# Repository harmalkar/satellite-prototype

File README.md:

# satellite-prototype
This repository contains all the files relating to BPP payload for SEDS UMD.

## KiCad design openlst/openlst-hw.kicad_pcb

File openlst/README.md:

# OpenLST Development/BPP Board

OpenLST board for SEDS@UMD modified by Nathan Kerns. The latest version of Kicad 6 Nightlies is required to view or modify the design. Recent pdf exports of the PCB and schematic are available in the pdf folder, but may not be completely up to date.

[Interactive BOM](https://harmalkar.github.io/satellite-prototype/ibom.html)

## BOM

BOM is automatically generated in KiCAD using "bom_csv_grouped_by_value" script, and manually separated into formats seen in bom folder. `openlst-bom.csv` contains entire BOM, `openlst-bom-digikey.csv` contains Digikey components, and `openlst-bom-mouser.csv` contains Mouser components.

## Power Budgets

3.3 V - 85 mA

* CC1110 - 50 mA max
* ASFL1-27MHz - 15 mA max
* TLV803S - 15 mA max
* PE4259 - <1 mA
* RFFM6404 - <1 mA

4.2 V - 600 mA

* RFFM6404 - 600 mA max

## Frequency Range

430-445 MHz

* CC1110 - 391-464 MHz
* SF2446E - 425-445 MHz
* RFFM6404 - 430-450 MHz

## Temperature Range

Constraining component is ASFL1-27MHz at -20 to 70 C

## PCB

Layers
* F.Cu - GND plane + signals
* In1.Cu - GND plane
* In2.Cu - Power planes
* B.Cu - GND plane + signals

50 ohm traces
* 6 mil (0.15 mm) clearance
* 13.4 mil (0.34 mm) width
* Via fence on 50x50 mil (1.27x1.27 mm) grid

Other traces
* 0.2 mm (8 mil) signal traces
* 0.3 mm (12 mil) power traces
* Power planes for high current paths

## Dimensions

* Board size: 50x43mm (not including SMA connector)
* Hole pattern: 43x36mm, M3 clearance hole (3.2mm diameter), screw head up to 6.5mm diameter

# Original readme

OpenLST Reference Hardware
==========================

This repository contains a KiCad project with a hardware reference
implementation for the OpenLST.  This design is a simplified version
of the Texas Instruments CC1110 432 MHz reference design.  A 1 watt
power amplifier module has been added to increase operating range.
The design is intended for use at 437 MHz, however, it may be modified
for use at other frequencies.

The user is responsible for obtaining and maintaining the necessary
license to operate this radio.  The example project uses frequencies
in the US Amateur Radio UHF band. Transmissions in this band require a
valid FCC license and compliance with CFR Part 97.

Contents
--------

This repository contains the following items:

  * [KiCAD 4.0](http://kicad-pcb.org/) project with self-contained part library
  * [Schematic](pdf/openlst-hw.pdf) in PDF form
  * [Bill of materials](bom/) with ordering information for components
  * [Gerber files](gerber/) for PCB fabrication

License & Legal Information
---------------------------

Copyright 2018 Planet Labs Inc. This work is licensed under a
Creative Commons Attribution-ShareAlike 4.0 International License.

This document may contain technology or software the export of which
is or may be restricted by the Export Administration Act and the
Export Administration Regulations (EAR), 15 C.F.R. parts
730-774. Diversion contrary to U.S. law is prohibited.

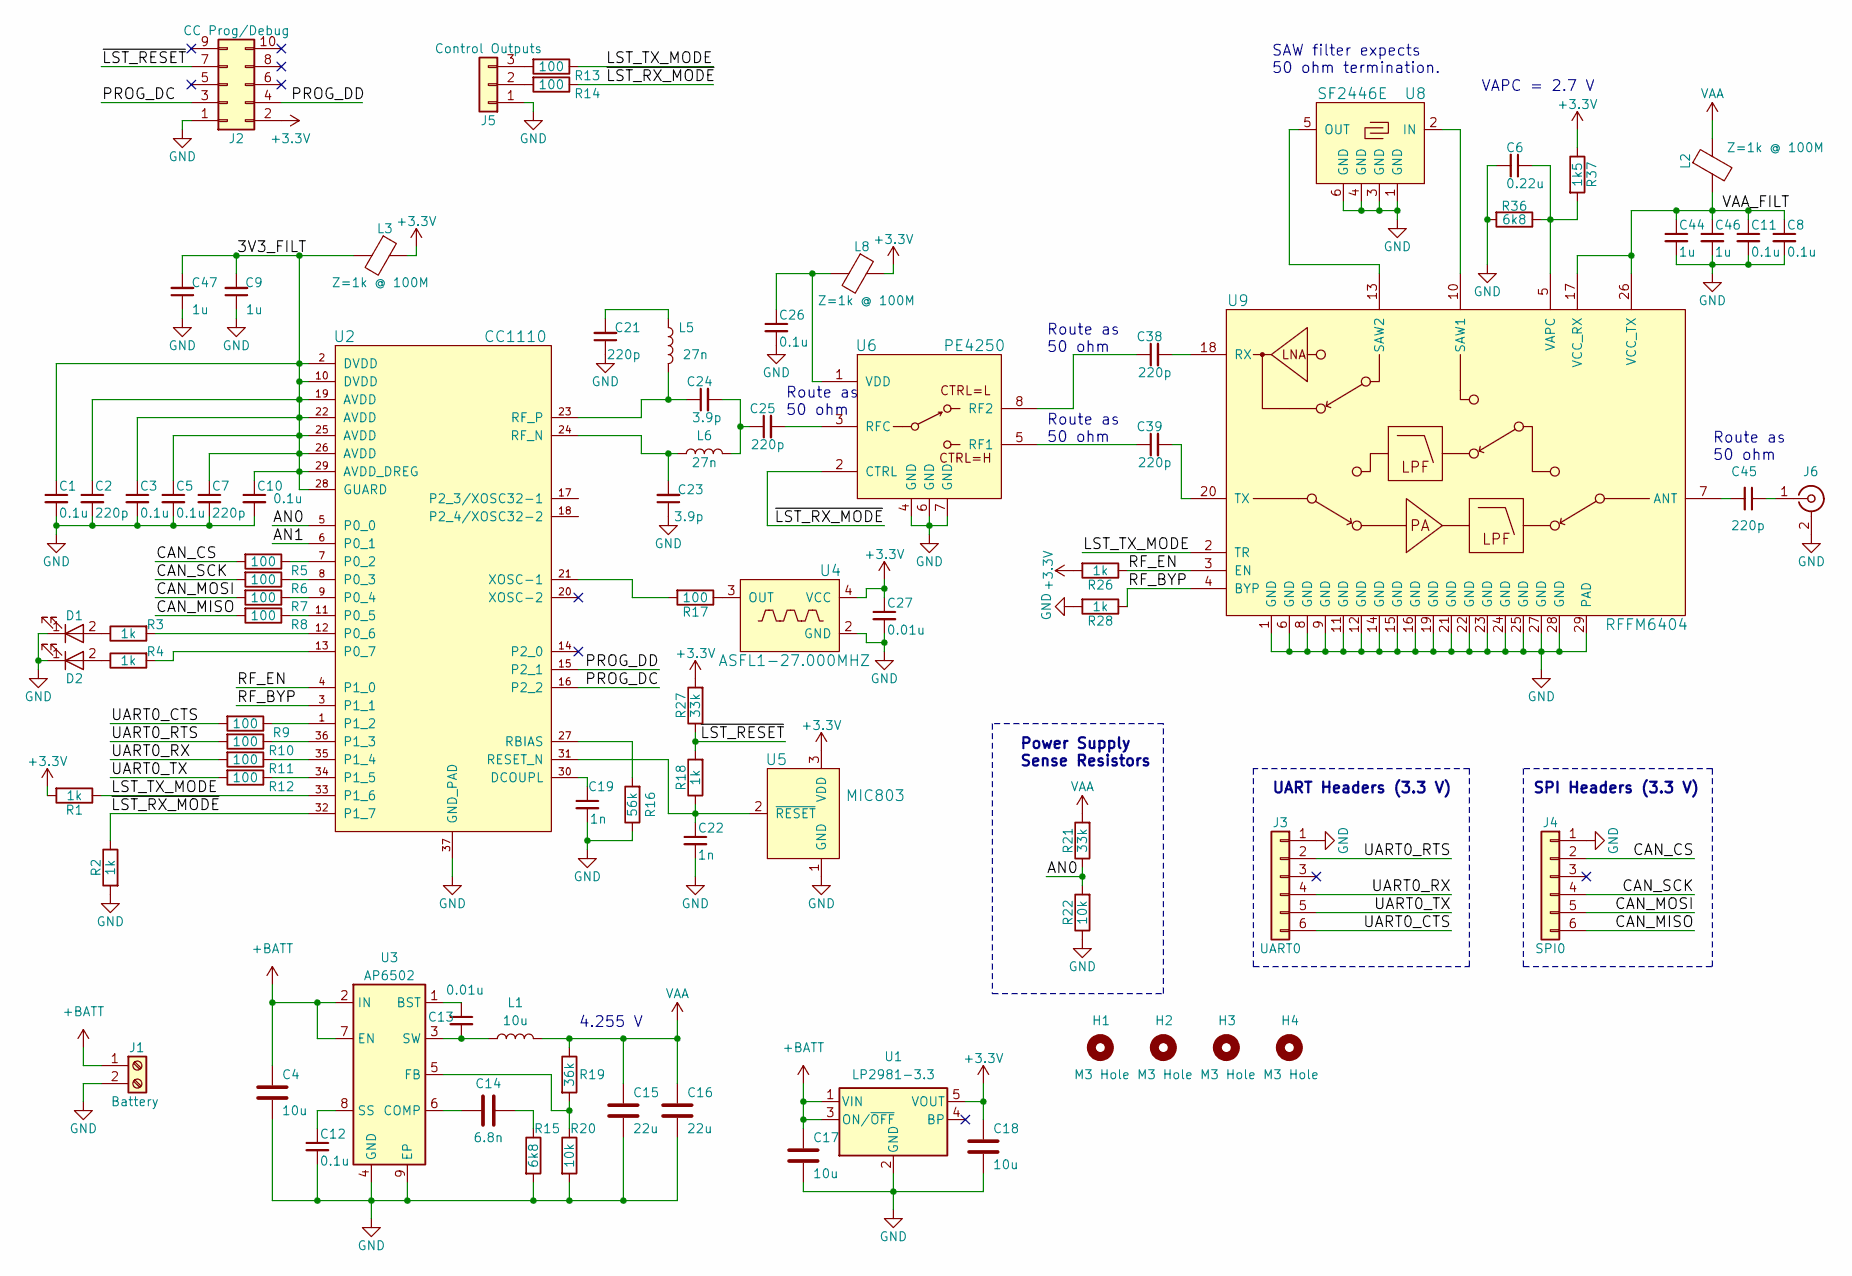
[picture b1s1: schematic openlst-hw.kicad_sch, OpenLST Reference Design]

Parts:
C1, C3, C5, C8, C10, C11, C12, C26: 0.1u; C_0603_1608Metric; ManufPN CL10B104MB8NNNC
C2, C7, C21, C25, C38, C39, C45: 220p; C_0402_1005Metric; ManufPN GCM1555C1H221JA16D
C4, C17, C18: 10u; C_0805_2012Metric; ManufPN GMK316AB7106KL-TR
C6: 0.22u; C_0603_1608Metric; ManufPN CL10B224KO8NNNC
C9, C44, C46, C47: 1u; C_0603_1608Metric; ManufPN CL10B105MO8NNWC
C13, C27: 0.01u; C_0603_1608Metric; ManufPN GCM188R72A103KA37D
C14: 6.8n; C_0603_1608Metric; ManufPN C0603C682K5RACTU
C15, C16: 22u; C_1210_3225Metric; ManufPN C3225X7R1C226M250AC
C19, C22: 1n; C_0603_1608Metric; ManufPN 06035C102KAT2A
C23, C24: 3.9p; C_0402_1005Metric; ManufPN AC0402CRNPO9BN3R9
D1, D2: LED; LED_0603_1608Metric; ManufPN 150060VS75000
H1, H2, H3, H4: M3 Hole; MountingHole_3.2mm_M3
J1: Battery; TerminalBlock_Phoenix_MKDS-1,5-2-5.08_1x02_P5.08mm_Horizont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; ManufPN 1729128
J2: CC Prog/Debug; PinHeader_2x05_P1.27mm_Vertical_SMD; ManufPN FTSH-105-01-F-DV-K-TR
J3: UART0; PinHeader_1x06_P2.54mm_Vertical
J4: SPI0; PinHeader_1x06_P2.54mm_Vertical
J5: Control Outputs; PinHeader_1x03_P2.54mm_Vertical
J6: ANT; SMA_Samtec_SMA-J-P-X-ST-EM1_EdgeMount; ManufPN SMA-J-P-H-ST-EM1
L1: 10u; L_Vishay_IFSC-1515AH_4x4x1.8mm; ManufPN ASPI-4030S-100M-T
L2, L3, L8: Z=1k @ 100M; L_0603_1608Metric; ManufPN PE-0603FB102ST
L5, L6: 27n; L_0402_1005Metric; ManufPN LQW15AN27NJ00D
R1, R2, R3, R4, R18, R26, R28: 1k; R_0603_1608Metric; ManufPN RC0603FR-071KL
R5, R6, R7, R8, R9, R10, R11, R12, R13, R14, R17: 100; R_0603_1608Metric; ManufPN RC0603FR-07100RL
R15, R36: 6k8; R_0603_1608Metric; ManufPN RC0603FR-076K8L
R16: 56k; R_0603_1608Metric; ManufPN RC0603FR-0756KL
R19: 36k; R_0603_1608Metric; ManufPN RC0603FR-0736KL
R20, R22: 10k; R_0603_1608Metric; ManufPN RC0603FR-0710KL
R21, R27: 33k; R_0603_1608Metric; ManufPN RMCF0603FT33K0
R37: 1k5; R_0603_1608Metric; ManufPN ERJ-3EKF1501V
U1: LP2981-3.3; SOT-23-5; ManufPN LP2981-33DBVR
U2: CC1110; TI_CC_QFN36; ManufPN CC1110F32RHHR
U3: AP6502; SOIC-8-1EP_3.9x4.9mm_P1.27mm_EP2.613x3.502mm; ManufPN AP6502SP-13
U4: ASFL1-27.000MHZ; Oscillator_SMD_SeikoEpson_SG8002LB-4Pin_5.0x3.2mm; ManufPN ASFL1-27.000MHZ-EK-T
U5: MIC803; SOT-23; ManufPN MIC803-29D3VM3-TR
U6: PE4250; MSOP-8_3x3mm_P0.65mm; ManufPN PE4250MLI-Z
U8: SF2446E; SAW-6_3.0mm; ManufPN SF2446E
U9: RFFM6404; Qorvo_LGA_28_ThermalVias; ManufPN RFFM6404TR13

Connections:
+3V3: C18.1, C27.1, J2.2, L3.1, L8.1, R1.2, R26.2, R27.2, R37.1, U1.5 (VOUT), U4.4 (VCC), U5.3 (VDD)
+BATT: C4.2, C17.2, J1.1, U1.1 (VIN), U1.3 (ON/~OFF), U3.2 (IN), U3.7 (EN)
/3V3_FILT: C1.1, C2.1, C3.1, C5.1, C7.1, C9.2, C10.1, C47.2, L3.2, U2.2 (DVDD), U2.10 (DVDD), U2.19 (AVDD), U2.22 (AVDD), U2.25 (AVDD), U2.26 (AVDD), U2.28 (GUARD), U2.29 (AVDD_DREG)
/AN0: R21.1, R22.2, U2.5 (P0_0)
/AN1: U2.6 (P0_1)
/CAN_CS: J4.2, R5.2
/CAN_MISO: J4.6, R8.2
/CAN_MOSI: J4.5, R7.2
/CAN_SCK: J4.4, R6.2
/LST_TX_MODE: R1.1, R13.1, U2.33 (P1_6), U9.2 (TR)
/PROG_DC: J2.3, U2.16 (P2_2)
/PROG_DD: J2.4, U2.15 (P2_1)
/RF_BYP: R28.1, U2.3 (P1_1), U9.4 (BYP)
/RF_EN: R26.1, U2.4 (P1_0), U9.3 (EN)
/UART0_CTS: J3.6, R9.2
/UART0_RTS: J3.2, R10.2
/UART0_RX: J3.4, R11.2
/UART0_TX: J3.5, R12.2
/VAA_FILT: C8.1, C11.1, C44.1, C46.1, L2.2, U9.17 (VCC_RX), U9.26 (VCC_TX)
/~LST_RESET: J2.7, R18.2, R27.1
/~LST_RX_MODE: R2.1, R14.1, U2.32 (P1_7), U6.2 (CTRL)
GND: C1.2, C2.2, C3.2, C4.1, C5.2, C6.2, C7.2, C8.2, C9.1, C10.2, C11.2, C12.2, C15.2, C16.2, C17.1, C18.2, C19.2, C21.1, C22.2, C23.1, C26.2, C27.2, C44.2, C46.2, C47.1, D1.1 (K), D2.1 (K), J1.2, J2.1, J3.1, J4.1, J5.1, J6.2 (Ext), R2.2, R15.2, R16.1, R20.2, R22.1, R28.2, R36.2, U1.2 (GND), U2.37 (GND_PAD), U3.4 (GND), U3.9 (EP), U4.2 (GND), U5.1 (GND), U6.4 (GND), U6.6 (GND), U6.7 (GND), U8.1 (GND), U8.3 (GND), U8.4 (GND), U8.6 (GND), U9.1 (GND), U9.6 (GND), U9.8 (GND), U9.9 (GND), U9.11 (GND), U9.12 (GND), U9.14 (GND), U9.15 (GND), U9.16 (GND), U9.19 (GND), U9.21 (GND), U9.22 (GND), U9.23 (GND), U9.24 (GND), U9.25 (GND), U9.27 (GND), U9.28 (GND), U9.29 (PAD)
unnamed: C6.1, R36.1, R37.2, U9.5 (VAPC)
unnamed: C12.1, U3.8 (SS)
unnamed: C13.1, U3.1 (BST)
unnamed: C13.2, L1.1, U3.3 (SW)
unnamed: C14.1, U3.6 (COMP)
unnamed: C14.2, R15.1
unnamed: C19.1, U2.30 (DCOUPL)
unnamed: C21.2, L5.1
unnamed: C22.1, R18.1, U2.31 (RESET_N), U5.2 (~RESET)
unnamed: C23.2, L6.1, U2.24 (RF_N)
unnamed: C24.1, L5.2, U2.23 (RF_P)
unnamed: C24.2, C25.1, L6.2
unnamed: C25.2, U6.3 (RFC)
unnamed: C26.1, L8.2, U6.1 (VDD)
unnamed: C38.1, U6.8 (RF2)
unnamed: C38.2, U9.18 (RX)
unnamed: C39.1, U6.5 (RF1)
unnamed: C39.2, U9.20 (TX)
unnamed: C45.1, J6.1 (In)
unnamed: C45.2, U9.7 (ANT)
unnamed: D1.2 (A), R3.1
unnamed: D2.2 (A), R4.1
unnamed: J5.2, R14.2
unnamed: J5.3, R13.2
unnamed: R3.2, U2.12 (P0_6)
unnamed: R4.2, U2.13 (P0_7)
unnamed: R5.1, U2.7 (P0_2)
unnamed: R6.1, U2.8 (P0_3)
unnamed: R7.1, U2.9 (P0_4)
unnamed: R8.1, U2.11 (P0_5)
unnamed: R9.1, U2.1 (P1_2)
unnamed: R10.1, U2.36 (P1_3)
unnamed: R11.1, U2.35 (P1_4)
unnamed: R12.1, U2.34 (P1_5)
unnamed: R16.2, U2.27 (RBIAS)
unnamed: R17.1, U4.3 (OUT)
unnamed: R17.2, U2.21 (XOSC-1)
unnamed: R19.2, R20.1, U3.5 (FB)
unnamed: U8.2 (IN), U9.10 (SAW1)
unnamed: U8.5 (OUT), U9.13 (SAW2)
VAA: C15.1, C16.1, L1.2, L2.1, R19.1, R21.2

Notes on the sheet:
4.255 V
Route as 50 ohm
Power Supply Sense Resistors
SAW filter expects 50 ohm termination.
UART Headers (3.3 V)
SPI Headers (3.3 V)
VAPC = 2.7 V

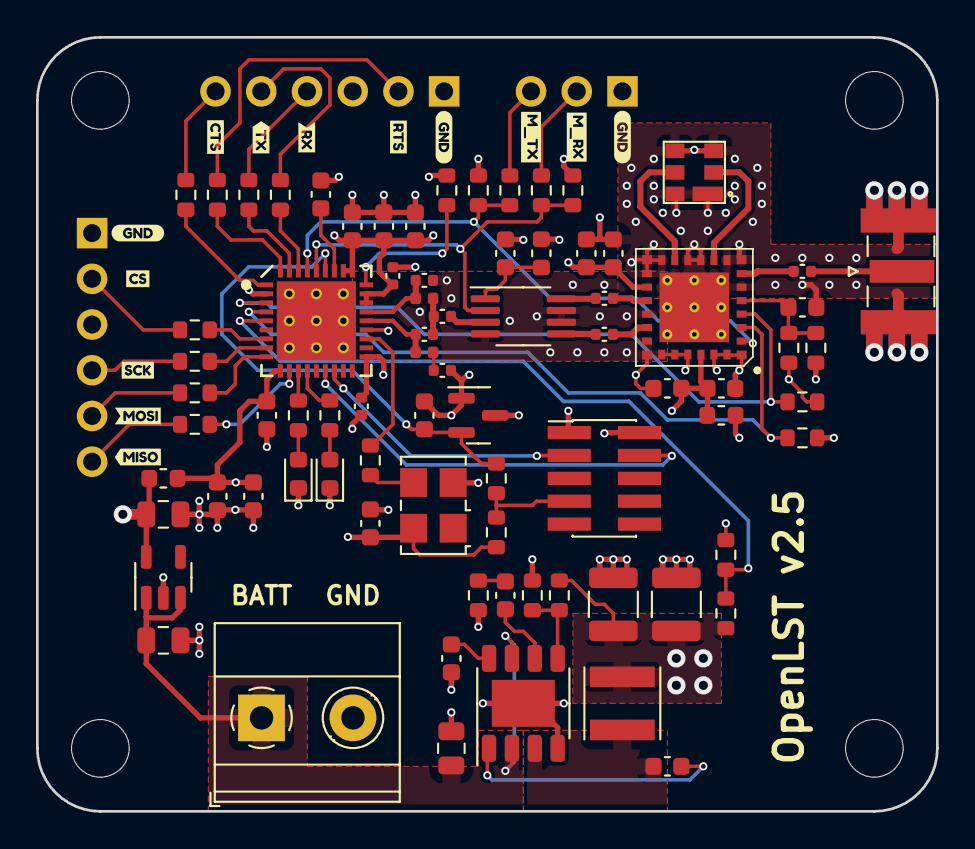
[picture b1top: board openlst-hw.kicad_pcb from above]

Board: 4 copper layers, 50.0 x 43.0 mm, 98 parts (0 on the bottom side), 62 nets.

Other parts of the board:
kibuzzard-610AE8D4: G***; kibuzzard-610AE8D4
kibuzzard-610AE8E6: G***; kibuzzard-610AE8E6
kibuzzard-610AE9EB: G***; kibuzzard-610AE9EB
kibuzzard-610AE73D, kibuzzard-610AE73D#2, kibuzzard-610AE73D#3: G***; kibuzzard-610AE73D
kibuzzard-610AE595: G***; kibuzzard-610AE595
kibuzzard-610AE658: G***; kibuzzard-610AE658
kibuzzard-610AE761: G***; kibuzzard-610AE761
kibuzzard-610AE773: G***; kibuzzard-610AE773
kibuzzard-610AE965: G***; kibuzzard-610AE965
kibuzzard-610AE972: G***; kibuzzard-610AE972
kibuzzard-610AEA01: G***; kibuzzard-610AEA01

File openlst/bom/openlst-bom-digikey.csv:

"Source:","/home/nathan/Documents/satellite-prototype/openlst/openlst-hw.kicad_sch"
"Date:","Thu Jul 15 17:48:57 2021"
"Tool:","Eeschema 5.99.0-unknown-e61b1f03b8~131~ubuntu20.04.1"
"Generator:","/usr/share/kicad-nightly/plugins/bom_csv_grouped_by_value.py"
"Component Count:","85"

"Item","Qty","Reference(s)","Value","LibPart","Footprint","Datasheet","Manuf","ManufPN","Supplier","SupplierPN"
"1","8","C1, C3, C5, C8, C10, C11, C12, C26","0.1u","openlst-hw:C_Small","Capacitor_SMD:C_0603_1608Metric","","Samsung","CL10B104MB8NNNC","Digikey","1276-1941-1-ND"
"2","7","C2, C7, C21, C25, C38, C39, C45","220p","openlst-hw:C_Small","Capacitor_SMD:C_0402_1005Metric","","Murata","GCM1555C1H221JA16D","Digikey","490-4927-1-ND"
"3","3","C4, C17, C18","10u","Device:C","Capacitor_SMD:C_0805_2012Metric","~","Taiyo Yuden","GMK316AB7106KL-TR","Digikey","587-3007-1-ND"
"4","1","C6","0.22u","openlst-hw:C_Small","Capacitor_SMD:C_0603_1608Metric","","Samsung","CL10B224KO8NNNC","Digikey","1276-1112-1-ND"
"5","4","C9, C44, C46, C47","1u","openlst-hw:C_Small","Capacitor_SMD:C_0603_1608Metric","","Samsung","CL10B105MO8NNWC","Digikey","1276-6524-1-ND"
"6","2","C13, C27","0.01u","openlst-hw:C_Small","Capacitor_SMD:C_0603_1608Metric","","Murata","GCM188R72A103KA37D","Digikey","490-4781-1-ND"
"7","1","C14","6.8n","Device:C","Capacitor_SMD:C_0603_1608Metric","~","KEMET","C0603C682K5RACTU","Digikey","399-1089-1-ND"
"8","2","C15, C16","22u","Device:C","Capacitor_SMD:C_1210_3225Metric","~","TDK","C3225X7R1C226M250AC","Digikey","445-3955-1-ND"
"9","2","C19, C22","1n","openlst-hw:C_Small","Capacitor_SMD:C_0603_1608Metric","","AVX","06035C102KAT2A","Digikey","478-1215-1-ND"
"10","2","C23, C24","3.9p","openlst-hw:C_Small","Capacitor_SMD:C_0402_1005Metric","","Yageo","AC0402CRNPO9BN3R9","Digikey","311-3054-1-ND"
"11","2","D1, D2","LED","openlst-hw:LED","LED_SMD:LED_0603_1608Metric","","Wurth","150060VS75000","Digikey","732-4980-1-ND"
"13","1","J1","Battery","Connector:Screw_Terminal_01x02","TerminalBlock_Phoenix:TerminalBlock_Phoenix_MKDS-1,5-2-5.08_1x02_P5.08mm_Horizontal","~","Phoenix Contact","1729128","Digikey","277-1247-ND"
"14","1","J2","CC Prog/Debug","openlst-hw:Conn_02x05_Odd_Even","Connector_PinHeader_1.27mm:PinHeader_2x05_P1.27mm_Vertical_SMD","","Samtec","FTSH-105-01-F-DV-K-TR","Digikey","SAM13160CT-ND"
"19","1","L1","10u","Device:L","Inductor_SMD:L_Vishay_IFSC-1515AH_4x4x1.8mm","https://abracon.com/Magnetics/power/ASPI-4030S.pdf","Abracon","ASPI-4030S-100M-T","Digikey","535-12314-1-ND"
"20","3","L2, L3, L8","Z=1k @ 100M","openlst-hw:Ferrite_Bead","Inductor_SMD:L_0603_1608Metric","","Pulse Electronics Network","PE-0603FB102ST","Digikey","553-2381-1-ND"
"21","2","L5, L6","27n","openlst-hw:L","Inductor_SMD:L_0402_1005Metric","","Murata","LQW15AN27NJ00D","Digikey","490-1151-1-ND"
"22","7","R1, R2, R3, R4, R18, R26, R28","1k","openlst-hw:R","Resistor_SMD:R_0603_1608Metric","","Yageo","RC0603FR-071KL","Digikey","311-1.00KHRCT-ND"
"23","11","R5, R6, R7, R8, R9, R10, R11, R12, R13, R14, R17","100","openlst-hw:R","Resistor_SMD:R_0603_1608Metric","","Yageo","RC0603FR-07100RL","Digikey","311-100HRCT-ND"
"24","2","R15, R36","6k8","openlst-hw:R","Resistor_SMD:R_0603_1608Metric","~","Yageo","RC0603FR-076K8L","Digkey","311-6.80KHRCT-ND"
"25","1","R16","56k","openlst-hw:R","Resistor_SMD:R_0603_1608Metric","","Yageo","RC0603FR-0756KL","Digikey","311-56KHRCT-ND"
"26","1","R19","36k","Device:R","Resistor_SMD:R_0603_1608Metric","~","Yageo","RC0603FR-0736KL","Digikey","311-36.0KHRCT-ND"
"27","2","R20, R22","10k","openlst-hw:R","Resistor_SMD:R_0603_1608Metric","~","Yageo","RC0603FR-0710KL","Digikey","311-10.0KHRCT-ND"
"28","2","R21, R27","33k","openlst-hw:R","Resistor_SMD:R_0603_1608Metric","","Stackpole Electronics","RMCF0603FT33K0","Digikey","RMCF0603FT33K0CT-ND"
"29","1","R37","1k5","openlst-hw:R","Resistor_SMD:R_0603_1608Metric","","Panasonic","ERJ-3EKF1501V","Digikey","P1.50KHCT-ND"
"30","1","U1","LP2981-3.3","Regulator_Linear:LP2985-3.3","Package_TO_SOT_SMD:SOT-23-5","https://www.ti.com/lit/ds/symlink/lp2981.pdf","Texas Instruments","LP2981-33DBVR","Digikey","296-17360-1-ND"
"32","1","U3","AP6502","Regulator_Switching:AP6502","Package_SO:SOIC-8-1EP_3.9x4.9mm_P1.27mm_EP2.62x3.51mm_ThermalVias","https://www.diodes.com/assets/Datasheets/AP6502.pdf","Diodes Inc","AP6502SP-13","Digikey","AP6502SP-13DICT-ND"
"33","1","U4","ASFL1-27.000MHZ","openlst-hw:FOX924","Oscillator:Oscillator_SMD_SeikoEpson_SG8002LB-4Pin_5.0x3.2mm","https://abracon.com/Oscillators/ASFL1.pdf","Abracon","ASFL1-27.000MHZ-EK-T","Digikey","535-9263-1-ND"
"34","1","U5","MIC803","openlst-hw:TLV803S","Package_TO_SOT_SMD:SOT-23","https://ww1.microchip.com/downloads/en/DeviceDoc/MIC803-3-Pi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","Microchip","MIC803-29D3VM3-TR","Digikey","576-3804-1-ND"
"35","1","U6","PE4250","openlst-hw:PE4250","Package_SO:MSOP-8_3x3mm_P0.65mm","https://www.psemi.com/pdf/datasheets/pe4250ds.pdf","pSemi","PE4250MLI-Z","Digikey","1046-1017-1-ND"

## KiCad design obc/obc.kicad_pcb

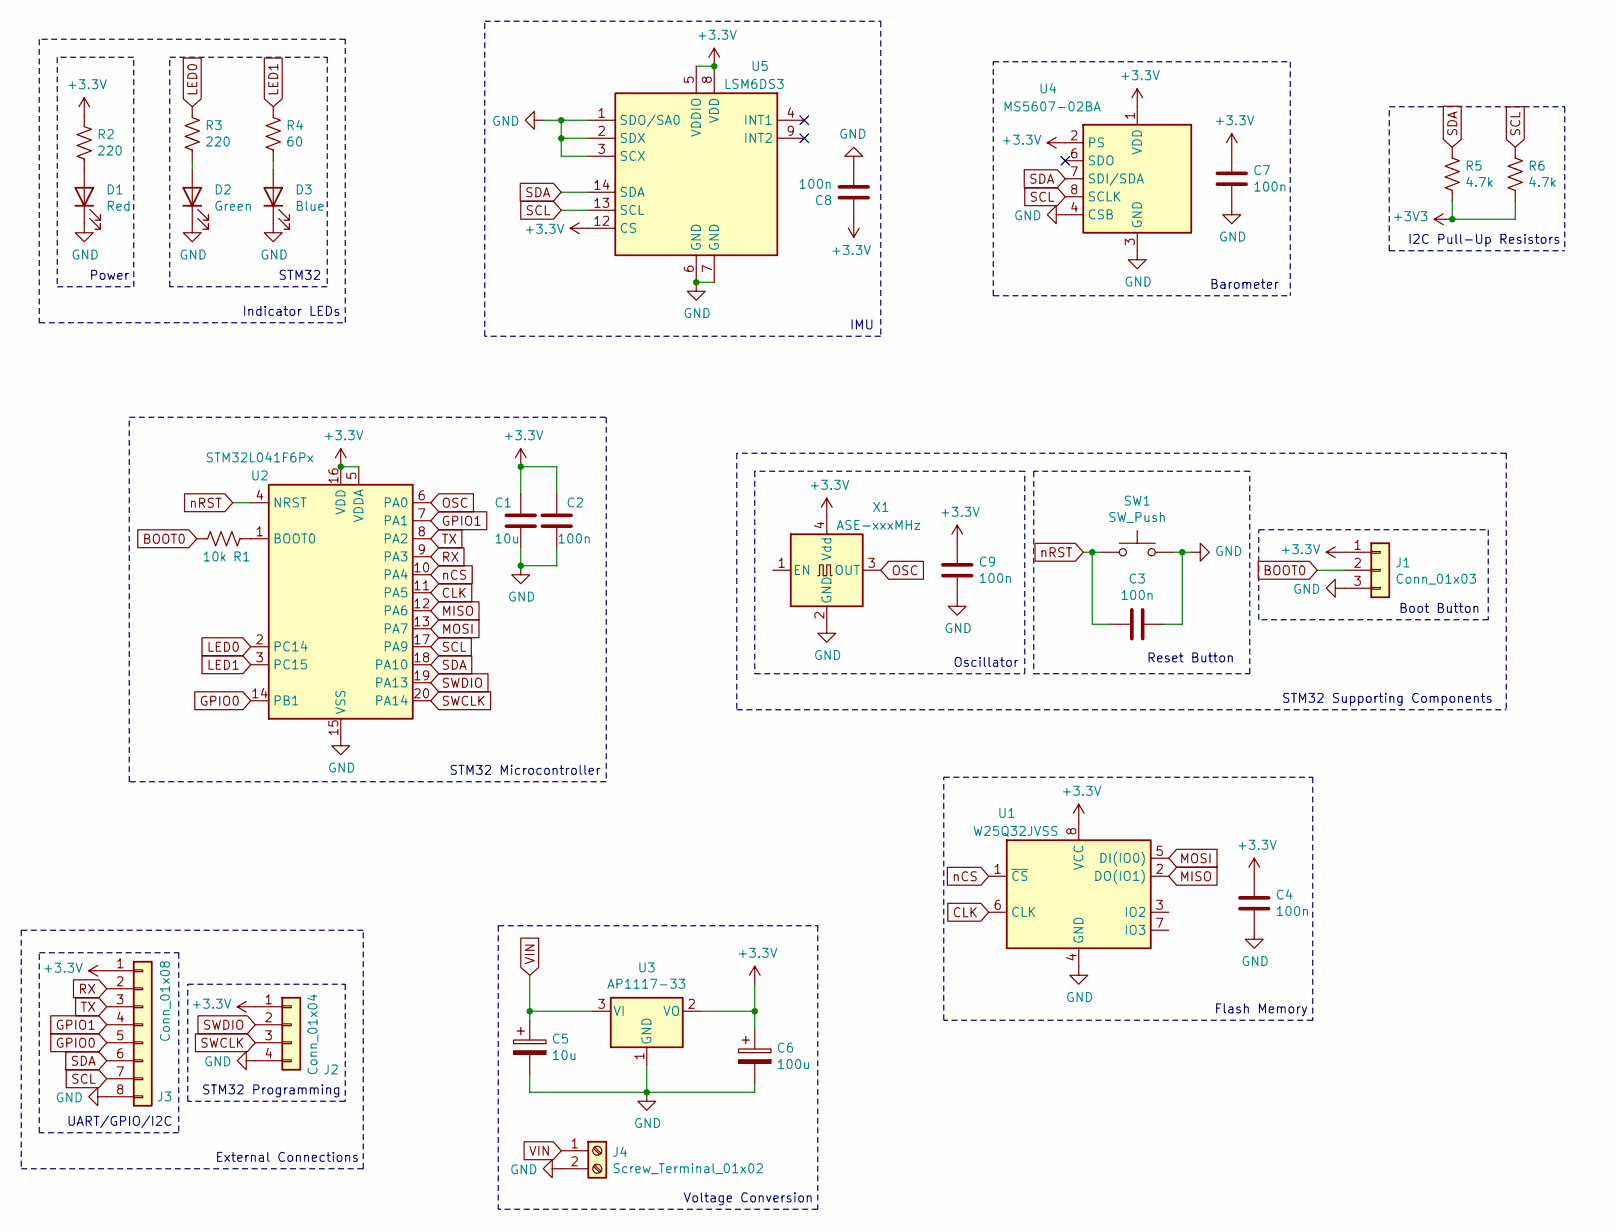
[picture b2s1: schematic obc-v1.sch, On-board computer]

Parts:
C1, C5: 10u; CP_Radial_D5.0mm_P2.00mm
C2, C3, C4, C7, C8, C9: 100n; C_0603_1608Metric
C6: 100u; CP_Radial_D12.5mm_P5.00mm
D1: Red; LED_0805_2012Metric
D2: Green; LED_0805_2012Metric
D3: Blue; LED_0805_2012Metric
J1: Conn_01x03; PinHeader_1x03_P2.54mm_Vertical
J2: Conn_01x04; PinHeader_1x04_P2.54mm_Vertical
J3: Conn_01x08; PinHeader_1x08_P2.54mm_Vertical
J4: Screw_Terminal_01x02; TerminalBlock_Phoenix_MKDS-1,5-2-5.08_1x02_P5.08mm_Horizont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
R1: 10k; R_0603_1608Metric
R2, R3: 220; R_0603_1608Metric
R4: 60; R_0603_1608Metric
R5, R6: 4.7k; R_0603_1608Metric
SW1: SW_Push; SW_PUSH_6mm
U1: W25Q32JVSS; SOIC-8_5.23x5.23mm_P1.27mm
U2: STM32L041F6Px; TSSOP-20_4.4x6.5mm_P0.65mm
U3: AP1117-33; SOT-223-3_TabPin2
U4: MS5607-02BA; LGA-8_3x5mm_P1.25mm
U5: LSM6DS3; LGA-14_3x2.5mm_P0.5mm_LayoutBorder3x4y
X1: ASE-xxxMHz; Oscillator_SMD_Abracon_ASE-4Pin_3.2x2.5mm

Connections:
+3V3: C1.2, C2.2, C4.1, C6.1, C7.1, C8.1, C9.1, J1.1, J2.1, J3.1, R2.1, U1.8 (VCC), U2.5 (VDDA), U2.16 (VDD), U3.2 (VO), U4.1 (VDD), U4.2 (PS), U5.5 (VDDIO), U5.8 (VDD), U5.12 (CS), X1.4 (Vdd)
BOOT0: J1.2, R1.2
CLK: U1.6 (CLK), U2.11 (PA5)
GPIO0: J3.5, U2.14 (PB1)
GPIO1: J3.4, U2.7 (PA1)
LED0: R3.1, U2.2 (PC14)
LED1: R4.1, U2.3 (PC15)
MISO: U1.2 (DO(IO1)), U2.12 (PA6)
MOSI: U1.5 (DI(IO0)), U2.13 (PA7)
unnamed: D1.2 (A), R2.2
unnamed: D2.2 (A), R3.2
unnamed: D3.2 (A), R4.2
unnamed: R1.1, U2.1 (BOOT0)
OSC: U2.6 (PA0), X1.3 (OUT)
RX: J3.2, U2.9 (PA3)
SCL: J3.7, R6.1, U2.17 (PA9), U4.8 (SCLK), U5.13 (SCL)
SDA: J3.6, R5.1, U2.18 (PA10), U4.7 (SDI/SDA), U5.14 (SDA)
SWCLK: J2.3, U2.20 (PA14)
SWDIO: J2.2, U2.19 (PA13)
TX: J3.3, U2.8 (PA2)
VIN: C5.1, J4.1, U3.3 (VI)
nCS: U1.1 (~CS), U2.10 (PA4)
nRST: C3.2, SW1.1, U2.4 (NRST)

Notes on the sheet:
STM32 Microcontroller
Oscillator
Reset Button
Boot Button
STM32 Supporting Components
I2C Pull-Up Resistors
STM32
Power
Indicator LEDs
IMU
Barometer
Flash Memory
STM32 Programming
UART/GPIO/I2C
External Connections
Voltage Conversion

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
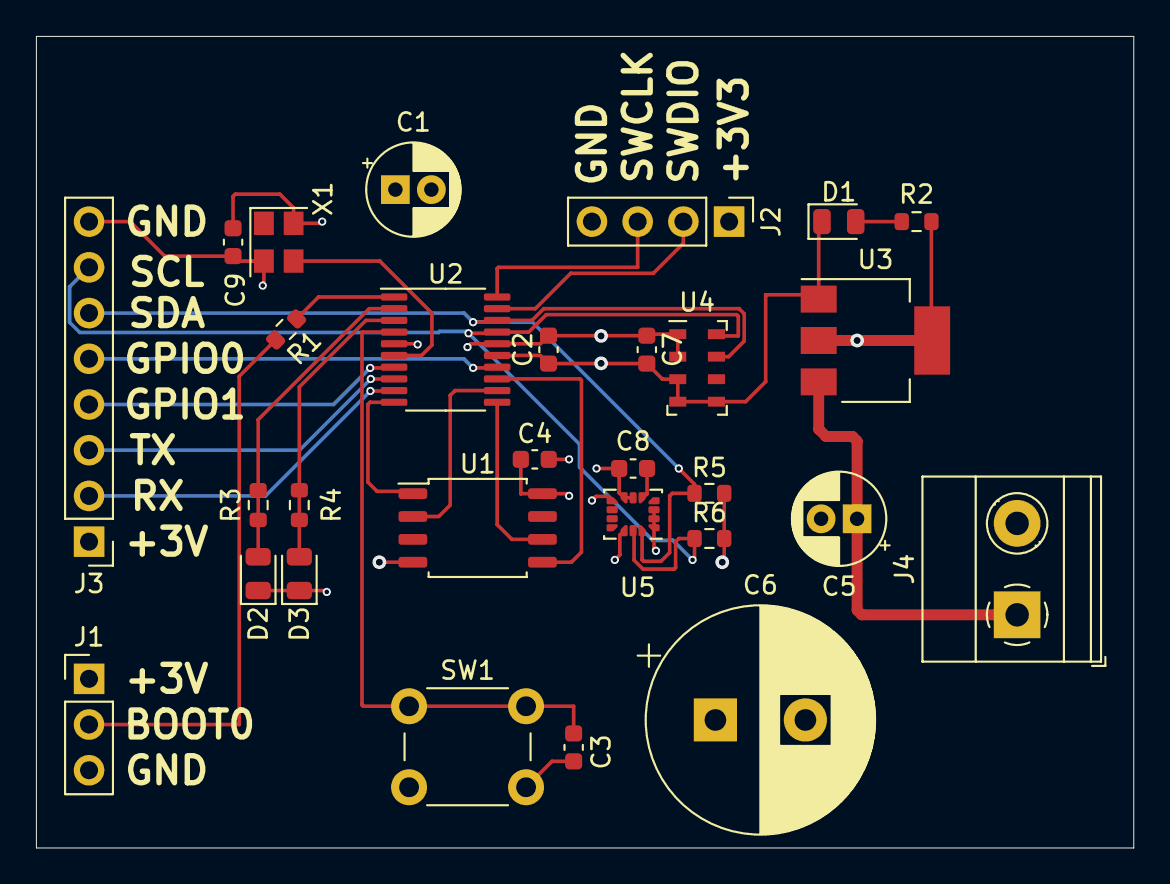
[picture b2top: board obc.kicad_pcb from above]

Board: 4 copper layers, 61.0 x 45.1 mm, 29 parts (0 on the bottom side), 24 nets.

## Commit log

2021-06-15 Add on-board computer schematics
2021-06-25 modified README.md
2021-06-26 Create imu_xyz_roll_pitch_yaw.ino
    IMU xyz coordinates and roll, pitch, and yaw code
2021-07-07 Added OpenLST files
2021-07-07 test 2
2021-07-11 Finished schematic, partially finished BOM, cleaned up old files
2021-07-11 Updated openlst readme
2021-07-15 Updated BOM
2021-07-17 Finalized BOM
2021-07-20 Started OpenLST PCB
2021-07-31 Finished OpenLST PCB
2021-08-04 Finals checks of PCB and gerber generation
2021-08-06 Added interactive BOM
2021-08-06 Moved interactive BOM to top level docs folder
2021-08-06 Updated step file and readme
2021-08-07 Added link to interactive BOM
2021-08-08 Started wiring diagram and software outline
2021-08-13 obc-v2: Add microcontroller, external oscillator, and flash memory
2021-08-19 obc-v2: Update microcontroller power circuitry
2021-08-26 obc-v2: Add BMI088 symbol
2021-08-26 obc-v2: Add IMU
2021-08-27 obc-v2: Add IMU interrupt and memory chip select connections
2021-08-27 obc-v2: Add barometer
2021-08-27 Add 1-wire interface for thermal sensors
2021-09-02 obc-v2: Add reset button
2021-09-02 obc-v2: Add voltage regulator
2021-09-09 obc-v2: Add voltage input and screw terminal
2021-09-13 obc-v2: Update 4MB flash chip to 1GB
2021-09-13 obc-v2: Add GPIO connector and LEDs
2021-09-13 obc-v2: Add pdf
2021-09-19 obc-v2: Fix reset button. Add debug header, RGB LED, and voltage divider circuit for measurement. Minor fixes to I2C bus, jumpers, and decoupling circuitry
2021-09-24 obc-v2: Fix reset circuit to prevent accidental triggering. Add i2c/uart connectors, SWD debugger header, and LED resistors.
2021-09-24 obc-v2: Add I2C pull-up resistors
2021-09-26 Worked on flight software structure
2021-09-28 obc-v2: Minor changes
2021-09-28 obc-v2: Add test pads
2021-09-28 obc-v2: Modify pinouts so that LED pins have PWM

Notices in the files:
openlst/openlst-hw.kicad_sch:
Copyright 2021 Nathan Kerns, Copyright 2018 Planet Labs Inc
